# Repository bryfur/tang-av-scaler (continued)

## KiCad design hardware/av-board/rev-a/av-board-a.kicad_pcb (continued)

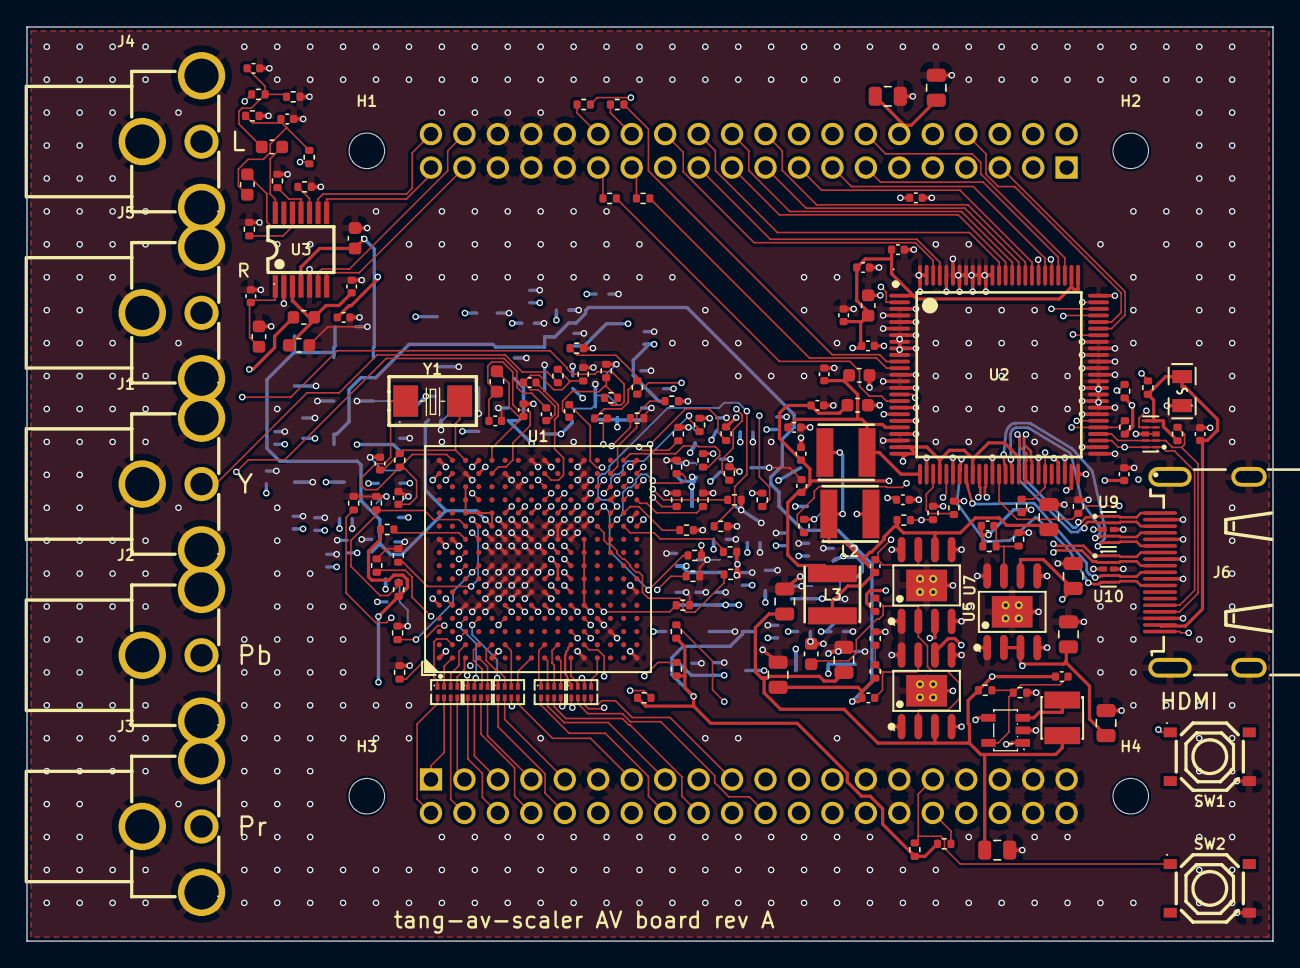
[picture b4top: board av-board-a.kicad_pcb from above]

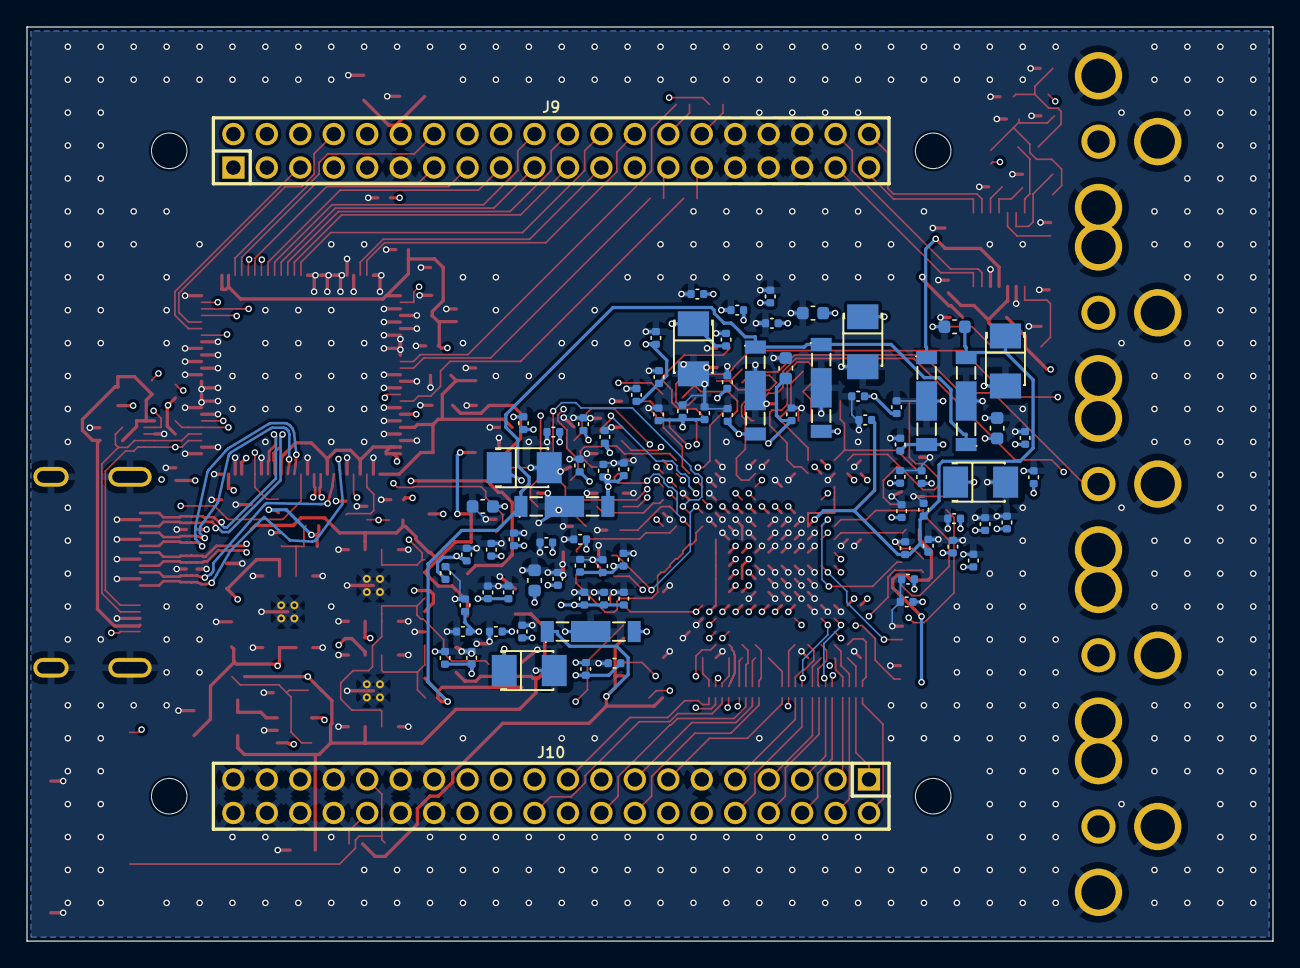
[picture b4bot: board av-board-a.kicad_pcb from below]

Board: 6 copper layers, 94.6 x 69.4 mm, 234 parts (83 on the bottom side), 166 nets.

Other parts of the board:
H1, H2, H3, H4: MountingHole_2.7mm_M2.5

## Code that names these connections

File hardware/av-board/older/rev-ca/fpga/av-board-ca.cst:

// av-board-ca.cst: FPGA pins (generated by rev-c/pinmap.py from the board's SOM nets)
IO_LOC "esp_cs" W22;  // J22 pin 2, bank 4
IO_PORT "esp_cs" IO_TYPE=LVCMOS33;
IO_LOC "esp_irq" W21;  // J22 pin 4, bank 4
IO_PORT "esp_irq" IO_TYPE=LVCMOS33;
IO_LOC "esp_miso" N17;  // J22 pin 14, bank 4
IO_PORT "esp_miso" IO_TYPE=LVCMOS33;
IO_LOC "esp_mosi" M16;  // J22 pin 16, bank 3
IO_PORT "esp_mosi" IO_TYPE=LVCMOS33;
IO_LOC "esp_rx" M17;  // J22 pin 10, bank 3
IO_PORT "esp_rx" IO_TYPE=LVCMOS33;
IO_LOC "esp_sck" P17;  // J22 pin 12, bank 4
IO_PORT "esp_sck" IO_TYPE=LVCMOS33;
IO_LOC "esp_tx" V20;  // J22 pin 6, bank 4, GCLKC_8 SGCLKC_5
IO_PORT "esp_tx" IO_TYPE=LVCMOS33;
IO_LOC "in_bck" E13;  // J21 pin 67, bank 2
IO_PORT "in_bck" IO_TYPE=LVCMOS33;
IO_LOC "in_c0" W12;  // J22 pin 86, bank 5, MGCLKC_6
IO_PORT "in_c0" IO_TYPE=LVCMOS33;
IO_LOC "in_c1" AA9;  // J22 pin 84, bank 5
IO_PORT "in_c1" IO_TYPE=LVCMOS33;
IO_LOC "in_c2" AA10;  // J22 pin 82, bank 5
IO_PORT "in_c2" IO_TYPE=LVCMOS33;
IO_LOC "in_c3" K13;  // J22 pin 63, bank 3
IO_PORT "in_c3" IO_TYPE=LVCMOS33;
IO_LOC "in_c4" AB10;  // J22 pin 80, bank 5
IO_PORT "in_c4" IO_TYPE=LVCMOS33;
IO_LOC "in_c5" AA11;  // J22 pin 78, bank 5
IO_PORT "in_c5" IO_TYPE=LVCMOS33;
IO_LOC "in_c6" K14;  // J22 pin 61, bank 3
IO_PORT "in_c6" IO_TYPE=LVCMOS33;
IO_LOC "in_c7" AB11;  // J22 pin 76, bank 5
IO_PORT "in_c7" IO_TYPE=LVCMOS33;
IO_LOC "in_de" Y13;  // J22 pin 56, bank 5
IO_PORT "in_de" IO_TYPE=LVCMOS33;
IO_LOC "in_dout" E14;  // J21 pin 65, bank 2
IO_PORT "in_dout" IO_TYPE=LVCMOS33;
IO_LOC "in_hs" AB13;  // J22 pin 62, bank 5
IO_PORT "in_hs" IO_TYPE=LVCMOS33;
IO_LOC "in_int" AA13;  // J22 pin 60, bank 5
IO_PORT "in_int" IO_TYPE=LVCMOS33;
IO_LOC "in_key1" A21;  // J21 pin 5, bank 2
IO_PORT "in_key1" IO_TYPE=LVCMOS33;
IO_LOC "in_key2" B21;  // J21 pin 7, bank 2
IO_PORT "in_key2" IO_TYPE=LVCMOS33;
IO_LOC "in_led" A20;  // J21 pin 11, bank 2
IO_PORT "in_led" IO_TYPE=LVCMOS33;
IO_LOC "in_llc" V13;  // J22 pin 88, bank 5, MGCLKT_7
IO_PORT "in_llc" IO_TYPE=LVCMOS33;
IO_LOC "in_lrck" G13;  // J21 pin 66, bank 3
IO_PORT "in_lrck" IO_TYPE=LVCMOS33;
IO_LOC "in_reset_n" T14;  // J22 pin 90, bank 5
IO_PORT "in_reset_n" IO_TYPE=LVCMOS33;
IO_LOC "in_scki" H13;  // J21 pin 68, bank 3
IO_PORT "in_scki" IO_TYPE=LVCMOS33;
IO_LOC "in_scl" W15;  // J22 pin 44, bank 5, SPI_CSN
IO_PORT "in_scl" IO_TYPE=LVCMOS33;
IO_LOC "in_sda" Y16;  // J22 pin 42, bank 5, SPI_MOSI
IO_PORT "in_sda" IO_TYPE=LVCMOS33;
IO_LOC "in_vs" AA14;  // J22 pin 58, bank 5
IO_PORT "in_vs" IO_TYPE=LVCMOS33;
IO_LOC "in_y0" W10;  // J22 pin 74, bank 5
IO_PORT "in_y0" IO_TYPE=LVCMOS33;
IO_LOC "in_y1" V10;  // J22 pin 68, bank 5
IO_PORT "in_y1" IO_TYPE=LVCMOS33;
IO_LOC "in_y2" AB12;  // J22 pin 66, bank 5
IO_PORT "in_y2" IO_TYPE=LVCMOS33;
IO_LOC "in_y3" Y12;  // J22 pin 64, bank 5, SGCLKC_6
IO_PORT "in_y3" IO_TYPE=LVCMOS33;
IO_LOC "in_y4" V14;  // J22 pin 54, bank 5, MGCLKC_7
IO_PORT "in_y4" IO_TYPE=LVCMOS33;
IO_LOC "in_y5" Y14;  // J22 pin 52, bank 5
IO_PORT "in_y5" IO_TYPE=LVCMOS33;
IO_LOC "in_y6" W14;  // J22 pin 48, bank 5
IO_PORT "in_y6" IO_TYPE=LVCMOS33;
IO_LOC "in_y7" V15;  // J22 pin 46, bank 5, SGCLKC_7
IO_PORT "in_y7" IO_TYPE=LVCMOS33;
IO_LOC "out_b0" A19;  // J21 pin 17, bank 2
IO_PORT "out_b0" IO_TYPE=LVCMOS33;
IO_LOC "out_b1" C19;  // J21 pin 16, bank 2, MGCLKC_0
IO_PORT "out_b1" IO_TYPE=LVCMOS33;
IO_LOC "out_b2" A18;  // J21 pin 19, bank 2
IO_PORT "out_b2" IO_TYPE=LVCMOS33;
IO_LOC "out_b3" B18;  // J21 pin 23, bank 2, SGCLKC_1
IO_PORT "out_b3" IO_TYPE=LVCMOS33;
IO_LOC "out_b4" E17;  // J21 pin 22, bank 2
IO_PORT "out_b4" IO_TYPE=LVCMOS33;
IO_LOC "out_b5" F16;  // J21 pin 24, bank 2
IO_PORT "out_b5" IO_TYPE=LVCMOS33;
IO_LOC "out_b6" C17;  // J21 pin 29, bank 2, MGCLKC_1
IO_PORT "out_b6" IO_TYPE=LVCMOS33;
IO_LOC "out_b7" D16;  // J21 pin 28, bank 2
IO_PORT "out_b7" IO_TYPE=LVCMOS33;
IO_LOC "out_cecclk" B13;  // J21 pin 53, bank 2
IO_PORT "out_cecclk" IO_TYPE=LVCMOS33;
IO_LOC "out_clk" A16;  // J21 pin 35, bank 2
IO_PORT "out_clk" IO_TYPE=LVCMOS33;
IO_LOC "out_de" B20;  // J21 pin 13, bank 2
IO_PORT "out_de" IO_TYPE=LVCMOS33;
IO_LOC "out_g0" E16;  // J21 pin 30, bank 2
IO_PORT "out_g0" IO_TYPE=LVCMOS33;
IO_LOC "out_g1" A15;  // J21 pin 37, bank 2
IO_PORT "out_g1" IO_TYPE=LVCMOS33;
IO_LOC "out_g2" D15;  // J21 pin 34, bank 2
IO_PORT "out_g2" IO_TYPE=LVCMOS33;
IO_LOC "out_g3" D14;  // J21 pin 36, bank 2
IO_PORT "out_g3" IO_TYPE=LVCMOS33;
IO_LOC "out_g4" B16;  // J21 pin 41, bank 2
IO_PORT "out_g4" IO_TYPE=LVCMOS33;
IO_LOC "out_g5" F15;  // J21 pin 40, bank 2
IO_PORT "out_g5" IO_TYPE=LVCMOS33;
IO_LOC "out_g6" F14;  // J21 pin 42, bank 2
IO_PORT "out_g6" IO_TYPE=LVCMOS33;
IO_LOC "out_g7" F13;  // J21 pin 44, bank 2
IO_PORT "out_g7" IO_TYPE=LVCMOS33;
IO_LOC "out_hsync" D19;  // J21 pin 10, bank 2, SGCLKC_0
IO_PORT "out_hsync" IO_TYPE=LVCMOS33;
IO_LOC "out_i2s0" E21;  // J20 pin 78, bank 2
IO_PORT "out_i2s0" IO_TYPE=LVCMOS33;
IO_LOC "out_int" G16;  // J21 pin 62, bank 3
IO_PORT "out_int" IO_TYPE=LVCMOS33;
IO_LOC "out_lrclk" C20;  // J21 pin 4, bank 2
IO_PORT "out_lrclk" IO_TYPE=LVCMOS33;
IO_LOC "out_mclk" D22;  // J20 pin 76, bank 2
IO_PORT "out_mclk" IO_TYPE=LVCMOS33;
IO_LOC "out_pd" B22;  // J20 pin 75, bank 2
IO_PORT "out_pd" IO_TYPE=LVCMOS33;
IO_LOC "out_r0" J16;  // J21 pin 48, bank 3
IO_PORT "out_r0" IO_TYPE=LVCMOS33;
IO_LOC "out_r1" J17;  // J21 pin 50, bank 3
IO_PORT "out_r1" IO_TYPE=LVCMOS33;
IO_LOC "out_r2" K17;  // J21 pin 52, bank 3
IO_PORT "out_r2" IO_TYPE=LVCMOS33;
IO_LOC "out_r3" B15;  // J21 pin 43, bank 2
IO_PORT "out_r3" IO_TYPE=LVCMOS33;
IO_LOC "out_r4" H15;  // J21 pin 54, bank 3
IO_PORT "out_r4" IO_TYPE=LVCMOS33;
IO_LOC "out_r5" J15;  // J21 pin 56, bank 3
IO_PORT "out_r5" IO_TYPE=LVCMOS33;
IO_LOC "out_r6" H14;  // J21 pin 58, bank 3
IO_PORT "out_r6" IO_TYPE=LVCMOS33;
IO_LOC "out_r7" A14;  // J21 pin 47, bank 2
IO_PORT "out_r7" IO_TYPE=LVCMOS33;
IO_LOC "out_scl" A13;  // J21 pin 49, bank 2
IO_PORT "out_scl" IO_TYPE=LVCMOS33;
IO_LOC "out_sclk" D21;  // J20 pin 80, bank 2
IO_PORT "out_sclk" IO_TYPE=LVCMOS33;
IO_LOC "out_sda" J14;  // J21 pin 60, bank 3
IO_PORT "out_sda" IO_TYPE=LVCMOS33;
IO_LOC "out_spdif" E22;  // J20 pin 74, bank 2
IO_PORT "out_spdif" IO_TYPE=LVCMOS33;
IO_LOC "out_vsync" D20;  // J21 pin 6, bank 2
IO_PORT "out_vsync" IO_TYPE=LVCMOS33;
IO_LOC "pll_clk2" D17;  // J21 pin 31, bank 2, MGCLKT_1
IO_PORT "pll_clk2" IO_TYPE=LVCMOS33;
IO_LOC "pll_scl" G15;  // J21 pin 64, bank 3
IO_PORT "pll_scl" IO_TYPE=LVCMOS33;
IO_LOC "pll_sda" C13;  // J21 pin 55, bank 2
IO_PORT "pll_sda" IO_TYPE=LVCMOS33;
IO_LOC "spdif_orx" C15;  // J21 pin 59, bank 2
IO_PORT "spdif_orx" IO_TYPE=LVCMOS33;
IO_LOC "spdif_rx" C14;  // J21 pin 61, bank 2
IO_PORT "spdif_rx" IO_TYPE=LVCMOS33;
IO_LOC "vga_scl_f" AA15;  // J22 pin 38, bank 5, SPI_MISO
IO_PORT "vga_scl_f" IO_TYPE=LVCMOS33;
IO_LOC "vga_sda_f" AB15;  // J22 pin 40, bank 5
IO_PORT "vga_sda_f" IO_TYPE=LVCMOS33;

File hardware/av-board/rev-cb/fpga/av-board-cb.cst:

// av-board-cb.cst: FPGA pins (generated by rev-c/pinmap.py from the board's SOM nets)
IO_LOC "cec_fpga" B13;  // J21 pin 53, bank 2
IO_PORT "cec_fpga" IO_TYPE=LVCMOS33;
IO_LOC "dbg0" AB16;  // J22 pin 36, bank 5
IO_PORT "dbg0" IO_TYPE=LVCMOS33;
IO_LOC "dbg1" L13;  // J22 pin 34, bank 3
IO_PORT "dbg1" IO_TYPE=LVCMOS33;
IO_LOC "dbg2" M13;  // J22 pin 32, bank 3
IO_PORT "dbg2" IO_TYPE=LVCMOS33;
IO_LOC "dbg3" AA16;  // J22 pin 30, bank 5
IO_PORT "dbg3" IO_TYPE=LVCMOS33;
IO_LOC "dbg4" AB17;  // J22 pin 28, bank 5
IO_PORT "dbg4" IO_TYPE=LVCMOS33;
IO_LOC "dbg5" Y17;  // J22 pin 26, bank 5
IO_PORT "dbg5" IO_TYPE=LVCMOS33;
IO_LOC "ddc_scl" J14;  // J21 pin 60, bank 3
IO_PORT "ddc_scl" IO_TYPE=LVCMOS33;
IO_LOC "ddc_sda" H14;  // J21 pin 58, bank 3
IO_PORT "ddc_sda" IO_TYPE=LVCMOS33;
IO_LOC "dp_hpd" A13;  // J21 pin 49, bank 2
IO_PORT "dp_hpd" IO_TYPE=LVCMOS33;
IO_LOC "dp_oe" G16;  // J21 pin 62, bank 3
IO_PORT "dp_oe" IO_TYPE=LVCMOS33;
IO_LOC "dp_scl" A14;  // J21 pin 47, bank 2
IO_PORT "dp_scl" IO_TYPE=LVCMOS33;
IO_LOC "dp_sda" B15;  // J21 pin 43, bank 2
IO_PORT "dp_sda" IO_TYPE=LVCMOS33;
IO_LOC "esp_cs" W22;  // J22 pin 2, bank 4
IO_PORT "esp_cs" IO_TYPE=LVCMOS33;
IO_LOC "esp_irq" W21;  // J22 pin 4, bank 4
IO_PORT "esp_irq" IO_TYPE=LVCMOS33;
IO_LOC "esp_miso" N17;  // J22 pin 14, bank 4
IO_PORT "esp_miso" IO_TYPE=LVCMOS33;
IO_LOC "esp_mosi" M16;  // J22 pin 16, bank 3
IO_PORT "esp_mosi" IO_TYPE=LVCMOS33;
IO_LOC "esp_rx" M17;  // J22 pin 10, bank 3
IO_PORT "esp_rx" IO_TYPE=LVCMOS33;
IO_LOC "esp_sck" P17;  // J22 pin 12, bank 4
IO_PORT "esp_sck" IO_TYPE=LVCMOS33;
IO_LOC "esp_tx" V20;  // J22 pin 6, bank 4, GCLKC_8 SGCLKC_5
IO_PORT "esp_tx" IO_TYPE=LVCMOS33;
IO_LOC "in_bck" E13;  // J21 pin 67, bank 2
IO_PORT "in_bck" IO_TYPE=LVCMOS33;
IO_LOC "in_c0" W12;  // J22 pin 86, bank 5, MGCLKC_6
IO_PORT "in_c0" IO_TYPE=LVCMOS33;
IO_LOC "in_c1" AA9;  // J22 pin 84, bank 5
IO_PORT "in_c1" IO_TYPE=LVCMOS33;
IO_LOC "in_c2" AA10;  // J22 pin 82, bank 5
IO_PORT "in_c2" IO_TYPE=LVCMOS33;
IO_LOC "in_c3" K13;  // J22 pin 63, bank 3
IO_PORT "in_c3" IO_TYPE=LVCMOS33;
IO_LOC "in_c4" AB10;  // J22 pin 80, bank 5
IO_PORT "in_c4" IO_TYPE=LVCMOS33;
IO_LOC "in_c5" AA11;  // J22 pin 78, bank 5
IO_PORT "in_c5" IO_TYPE=LVCMOS33;
IO_LOC "in_c6" K14;  // J22 pin 61, bank 3
IO_PORT "in_c6" IO_TYPE=LVCMOS33;
IO_LOC "in_c7" AB11;  // J22 pin 76, bank 5
IO_PORT "in_c7" IO_TYPE=LVCMOS33;
IO_LOC "in_de" Y13;  // J22 pin 56, bank 5
IO_PORT "in_de" IO_TYPE=LVCMOS33;
IO_LOC "in_dout" E14;  // J21 pin 65, bank 2
IO_PORT "in_dout" IO_TYPE=LVCMOS33;
IO_LOC "in_hs" AB13;  // J22 pin 62, bank 5
IO_PORT "in_hs" IO_TYPE=LVCMOS33;
IO_LOC "in_int" AA13;  // J22 pin 60, bank 5
IO_PORT "in_int" IO_TYPE=LVCMOS33;
IO_LOC "in_key1" B22;  // J20 pin 75, bank 2
IO_PORT "in_key1" IO_TYPE=LVCMOS33;
IO_LOC "in_key2" C22;  // J20 pin 73, bank 2
IO_PORT "in_key2" IO_TYPE=LVCMOS33;
IO_LOC "in_led" E18;  // J20 pin 71, bank 2
IO_PORT "in_led" IO_TYPE=LVCMOS33;
IO_LOC "in_llc" V13;  // J22 pin 88, bank 5, MGCLKT_7
IO_PORT "in_llc" IO_TYPE=LVCMOS33;
IO_LOC "in_lrck" G13;  // J21 pin 66, bank 3
IO_PORT "in_lrck" IO_TYPE=LVCMOS33;
IO_LOC "in_reset_n" T14;  // J22 pin 90, bank 5
IO_PORT "in_reset_n" IO_TYPE=LVCMOS33;
IO_LOC "in_scki" H13;  // J21 pin 68, bank 3
IO_PORT "in_scki" IO_TYPE=LVCMOS33;
IO_LOC "in_scl" W15;  // J22 pin 44, bank 5, SPI_CSN
IO_PORT "in_scl" IO_TYPE=LVCMOS33;
IO_LOC "in_sda" Y16;  // J22 pin 42, bank 5, SPI_MOSI
IO_PORT "in_sda" IO_TYPE=LVCMOS33;
IO_LOC "in_vs" AA14;  // J22 pin 58, bank 5
IO_PORT "in_vs" IO_TYPE=LVCMOS33;
IO_LOC "in_y0" W10;  // J22 pin 74, bank 5
IO_PORT "in_y0" IO_TYPE=LVCMOS33;
IO_LOC "in_y1" V10;  // J22 pin 68, bank 5
IO_PORT "in_y1" IO_TYPE=LVCMOS33;
IO_LOC "in_y2" AB12;  // J22 pin 66, bank 5
IO_PORT "in_y2" IO_TYPE=LVCMOS33;
IO_LOC "in_y3" Y12;  // J22 pin 64, bank 5, SGCLKC_6
IO_PORT "in_y3" IO_TYPE=LVCMOS33;
IO_LOC "in_y4" V14;  // J22 pin 54, bank 5, MGCLKC_7
IO_PORT "in_y4" IO_TYPE=LVCMOS33;
IO_LOC "in_y5" Y14;  // J22 pin 52, bank 5
IO_PORT "in_y5" IO_TYPE=LVCMOS33;
IO_LOC "in_y6" W14;  // J22 pin 48, bank 5
IO_PORT "in_y6" IO_TYPE=LVCMOS33;
IO_LOC "in_y7" V15;  // J22 pin 46, bank 5, SGCLKC_7
IO_PORT "in_y7" IO_TYPE=LVCMOS33;
IO_LOC "pll_clk2" D17;  // J21 pin 31, bank 2, MGCLKT_1
IO_PORT "pll_clk2" IO_TYPE=LVCMOS33;
IO_LOC "pll_scl" G15;  // J21 pin 64, bank 3
IO_PORT "pll_scl" IO_TYPE=LVCMOS33;
IO_LOC "pll_sda" C13;  // J21 pin 55, bank 2
IO_PORT "pll_sda" IO_TYPE=LVCMOS33;
IO_LOC "spdif_orx" C15;  // J21 pin 59, bank 2
IO_PORT "spdif_orx" IO_TYPE=LVCMOS33;
IO_LOC "spdif_rx" C14;  // J21 pin 61, bank 2
IO_PORT "spdif_rx" IO_TYPE=LVCMOS33;
IO_LOC "vga_scl_f" AA15;  // J22 pin 38, bank 5, SPI_MISO
IO_PORT "vga_scl_f" IO_TYPE=LVCMOS33;
IO_LOC "vga_sda_f" AB15;  // J22 pin 40, bank 5
IO_PORT "vga_sda_f" IO_TYPE=LVCMOS33;

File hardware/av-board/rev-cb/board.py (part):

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    for pol, p in (("P", "p"), ("N", "n")):
        u2[pin("OUT_%s%s" % ({"CK": "CLK"}.get(ch, ch), p))] = "TMDS_%s_%s" % (ch, pol)
# Hot plug: the receptacle's HPD in (10 k down already), out to the FPGA [Pin Functions]
u2[pin("HPD_SNK")] = "HDMI_HPD"
u2[pin("HPD_SRC")] = "DP_HPD"
# DDC: the receptacle side (2 k to HDMI 5 V already) and the FPGA's side, 2 k to 3.3 V [Fig. 33];
# the retimer snoops it (TMDS_CLOCK_RATIO for HDMI 2.0 rates) and passes it through
u2[pin("SDA_SNK")] = "HDMI_SDA"
u2[pin("SCL_SNK")] = "HDMI_SCL"
u2[pin("SDA_SRC")] = "DDC_SDA"
u2[pin("SCL_SRC")] = "DDC_SCL"
R("2k", "3V3", "DDC_SDA")
R("2k", "3V3", "DDC_SCL")
# Control by I2C from the FPGA (HDMI 2.0 tuning needs it [10.3.1]): I2C_EN/PIN high; A0 low (10 k
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# TX_TERM_CTL and SWAP/POL open (I2C sets them). OE from the FPGA with 100 nF to GND (it must rise
# after the supplies [10.2.1]; its internal 150-250 k pull-up and the 100 nF also make a power-on
# delay should the FPGA leave it floating)
u2[pin("I2C_EN/PIN")] = "DP_I2C_EN"
R("10k", "3V3", "DP_I2C_EN")
u2[pin("EQ_SEL/A0")] = "DP_A0"
R("10k", "DP_A0", "GND")
u2[pin("SCL_CTL")] = "DP_SCL"
u2[pin("SDA_CTL")] = "DP_SDA"
R("4.7k", "3V3", "DP_SCL")
R("4.7k", "3V3", "DP_SDA")
u2[pin("OE")] = "DP_OE"
C("100n", "DP_OE")
# Vsadj: 7.06 k 0.5 % for the RGZ package's HDMI 2.0 and 1.4b swing [10.3.1]
u2[pin("VSADJ")] = "DP_VSADJ"
R("7.06k", "DP_VSADJ", "GND")
part("U2", "SN65DP159RGZR", "lcsc:SN65DP159RGZR", "lcsc:VQFN-48_L7.0-W7.0-P0.50-BL-EP4.1", "C179676", u2)
# Decoupling [Fig. 33]: VCC 10 uF + 0.1 uF + 0.01 uF (two pins); VDD 10 uF and 0.1 uF at each of
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# separate pads, not a header: a probe slipping on a header would short 5 V onto the 1.1 V core.
# TEST_PADS: ref -> its silkscreen label
TEST_PADS = {}
for net, at, label in (("+5V", _by("+5V", "VBUS_IN"), "+5V"), ("3V6", _by("3V6", "SW_3V6"), "3V6"),
                       ("3V3", "U5.6", "3V3"), ("1V8A", "U6.6", "1V8"), ("1V1", _by("1V1", "SW_1V1"), "1V1"),
                       ("3V0", "U24.5", "3V0"), ("2V5", "U18.5", "2V5"), ("5VA", "U12.5", "5VA")):
    ref = nxt("TP")
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
# the SN65DP159's FPGA lines -> its pad; CEC's at the retimer too (its FET sits by the receptacle)
DP159_PADS = {net: num for num, net in u2.items() if net in ("DP_SCL", "DP_SDA", "DDC_SCL", "DDC_SDA", "DP_HPD", "DP_OE")}
DP159_PADS["CEC_FPGA"] = pin("HPD_SNK")
dp_pins, dp_body = chip_pins("lcsc:VQFN-48_L7.0-W7.0-P0.50-BL-EP4.1", floor.DP159_AT, floor.DP159_ANGLE, DP159_PADS)
SOM_NETS = som(common_groups(spdif_at=floor.SPDIF_AT_CB, ui_at=floor.UI_AT_CB) + [("dp159", dp_pins, {}, dp_body),
               ("debug", point(DEBUG, floor.DEBUG_AT_CB), {})], transceiver_lanes=LANES, rev=REV)
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
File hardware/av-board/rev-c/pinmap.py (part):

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The FPGA takes any signal on any I/O, so each group of signals (one chip's bus) takes the free
3.3 V I/O pins nearest that chip (floor.py's geometry), a clock input a clock-capable pin, and a
bus keeps the order its lines leave the chip along the connector (fewer crossings: gen_pcb.py
counts them). Dedicated pins (JTAG, RECONFIG_N, DONE, READY, the MODE straps, the transceivers,
the 5 V input) are fixed by the SOM. The result is written to the board (the receptacles' nets)
and to fpga/<rev>.cst, the Gowin constraints the gateware is built with.
"""
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

def transceivers(lanes):
    """{lane: net prefix}: the lanes' TX pins -> <prefix>_P/_N; and REFCLK0 -> SER_REFCLK_P/_N."""
    out = {}
    for ref, pins in PINS.items():
        for pin, (net, _, _) in pins.items():
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                elif net == "Q0_L%d.TXN" % lane:
                    out[(ref, pin)] = prefix + "_N"
            if net == "Q0_REFCLK0.P":
                out[(ref, pin)] = "SER_REFCLK_P"
            elif net == "Q0_REFCLK0.N":
                out[(ref, pin)] = "SER_REFCLK_N"
    return out


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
